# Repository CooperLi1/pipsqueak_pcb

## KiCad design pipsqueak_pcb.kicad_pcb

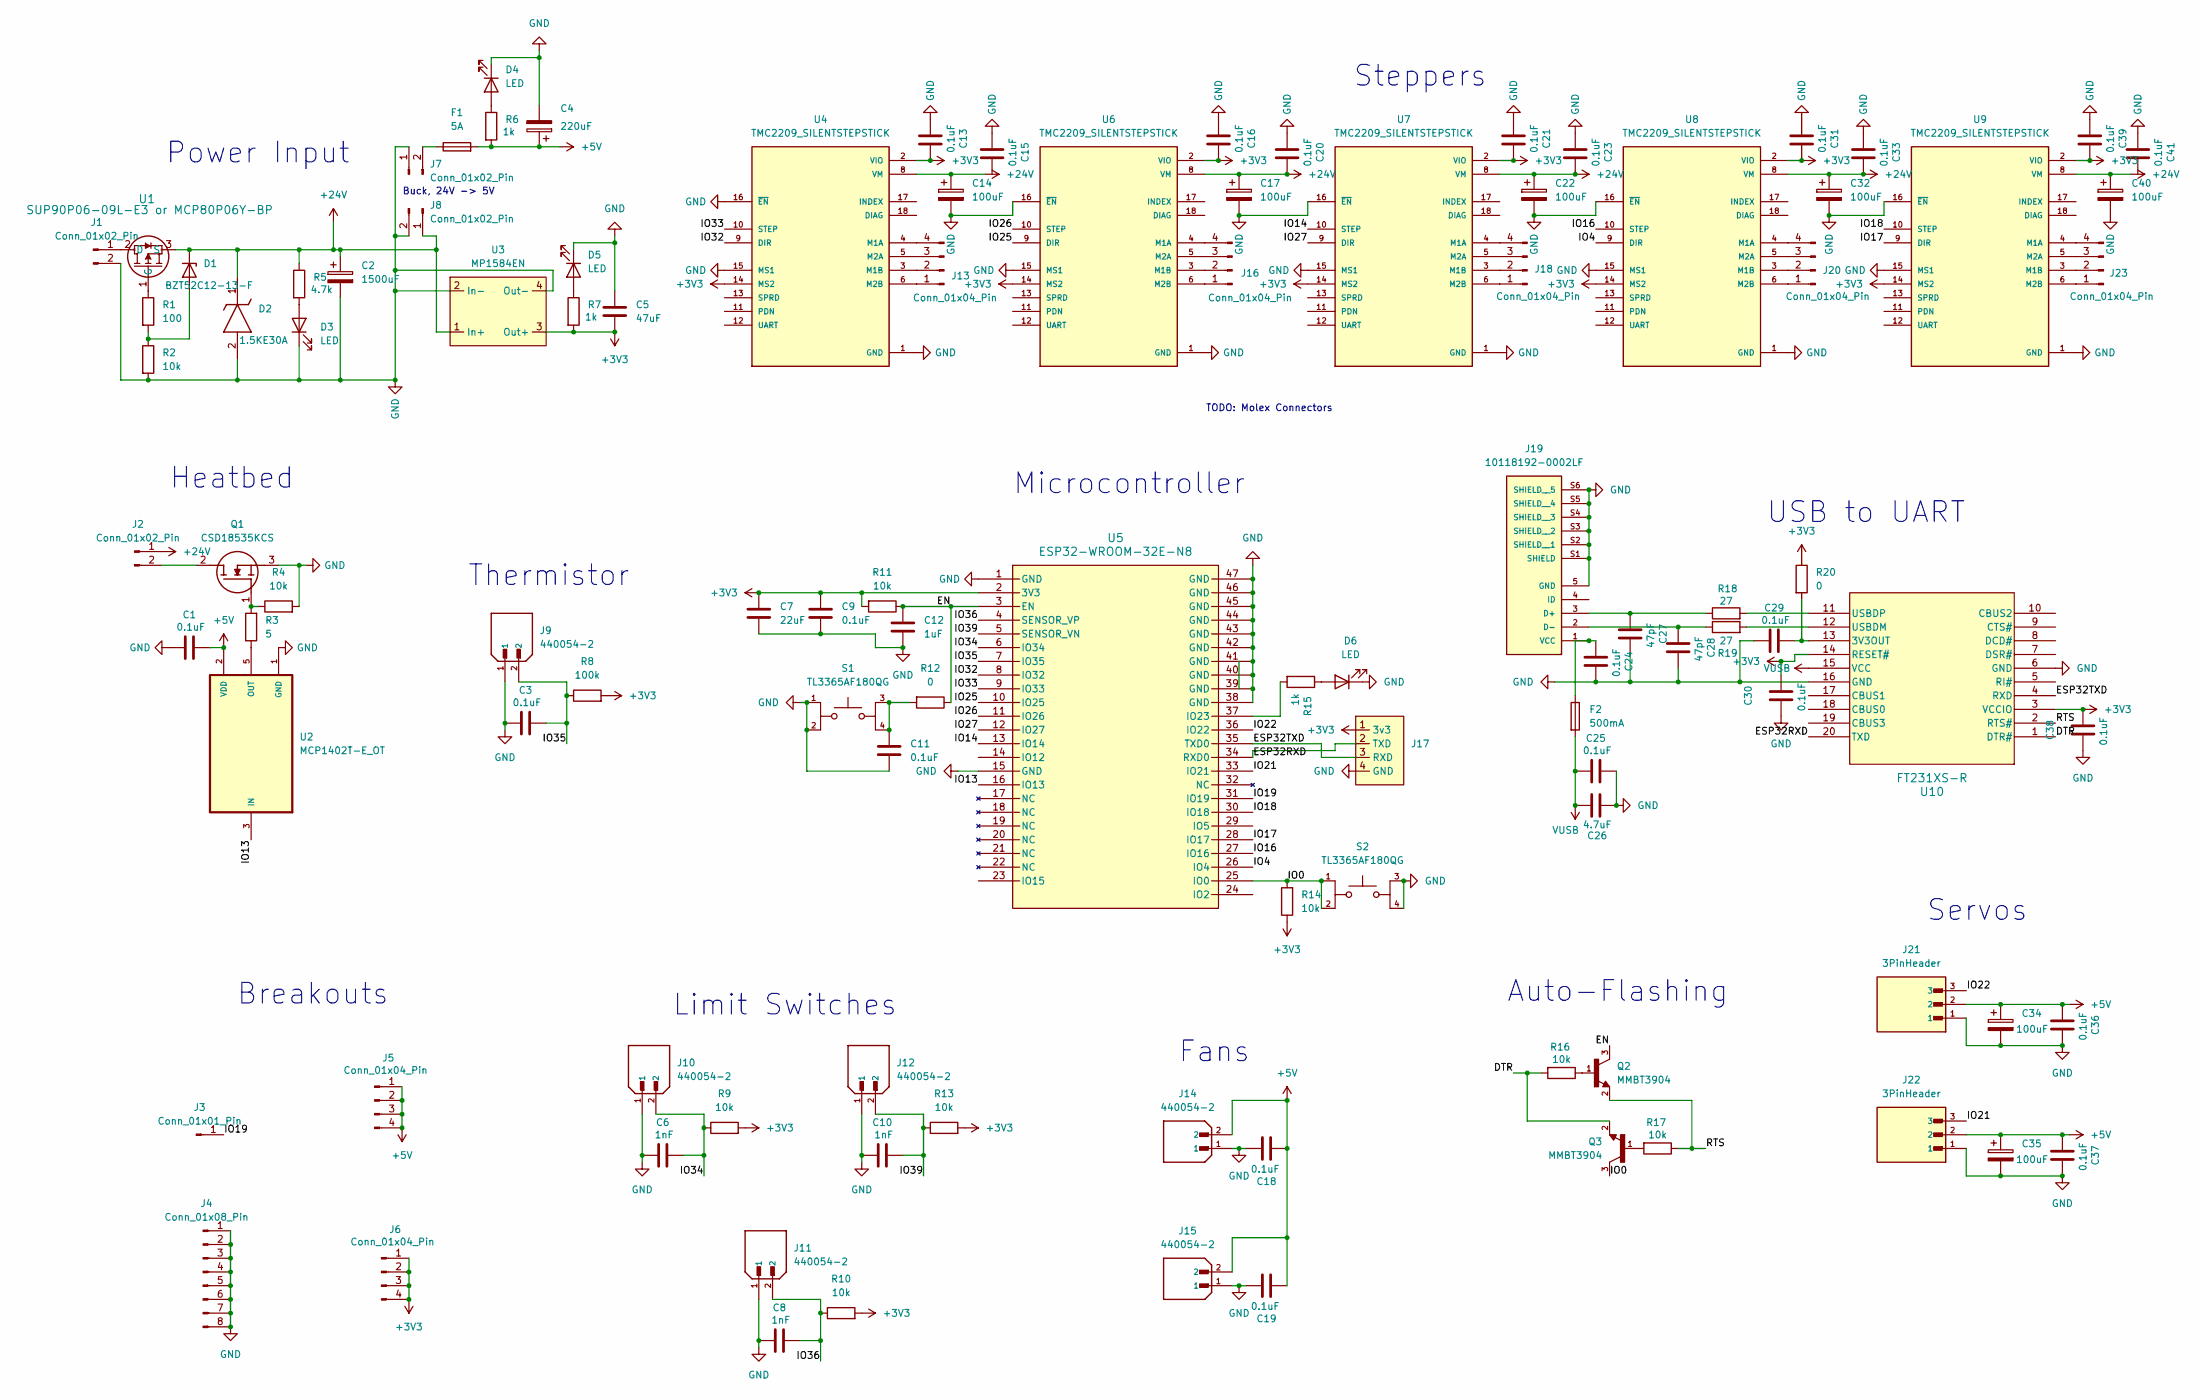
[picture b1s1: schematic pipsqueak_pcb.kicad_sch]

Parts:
C1, C3, C9, C11, C13, C15, C16, C18, C19, C20, C21, C23, C24, C25, C29, C30, C31, C33, C36, C37, C38, C39, C41: 0.1uF; C_0603_1608Metric
C2: 1500uF; CP_Radial_D18.0mm_P7.50mm
C4: 220uF; C_Elec_6.3x7.7
C5: 47uF; C_1206_3216Metric
C6, C8, C10: 1nF; C_0603_1608Metric
C7: 22uF; C_1206_3216Metric
C12: 1uF; C_0603_1608Metric
C14, C17, C22, C32, C40: 100uF; CP_Radial_D8.0mm_P3.50mm
C26: 4.7uF; C_1206_3216Metric
C27, C28: 47pF; C_0603_1608Metric
C34, C35: 100uF; CP_Elec_6.3x5.4
D1: BZT52C12-13-F; D_SOD-123
D2: 1.5KE30A; DIOAD2920W106L900D505; Mouser Part Number 511-1.5KE30A
D3, D4, D5, D6: LED; LED_0805_2012Metric
F1: 5A; Fuse_2920_7451Metric
F2: 500mA; Fuse_1812_4532Metric
J1, J2: Conn_01x02_Pin; AMASS_XT30U-F_1x02_P5.0mm_Vertical
J3: Conn_01x01_Pin; PinHeader_1x01_P2.54mm_Vertical
J4: Conn_01x08_Pin; PinHeader_1x08_P2.54mm_Vertical
J5, J6: Conn_01x04_Pin; PinHeader_1x04_P2.54mm_Vertical
J7, J8: Conn_01x02_Pin; Molex_KK-254_AE-6410-02A_1x02_P2.54mm_Vertical
J9, J10, J11, J12, J14, J15: 440054-2; TE_440054-2; PARTREV F9
J13, J16, J18, J20, J23: Conn_01x04_Pin; Molex_KK-254_AE-6410-04A_1x04_P2.54mm_Vertical
J17: 4HoleHeader
J19: 10118192-0002LF; AMPHENOL_10118192-0002LF; PARTREV B
J21, J22: 3PinHeader; HARWIN_M20-9990346
Q1: CSD18535KCS; TO254P470X1016X1611-3P; Mouser Part Number 595-CSD18535KCS
Q2, Q3: MMBT3904; TRANS_MMBT3904; PARTREV 2025-06-30
R1: 100; R_1206_3216Metric
R2, R4, R9, R10, R11, R13, R14, R16, R17: 10k; R_0603_1608Metric
R3: 5; R_0805_2012Metric
R5: 4.7k; R_0603_1608Metric
R6, R7, R15: 1k; R_0603_1608Metric
R8: 100k; R_0603_1608Metric
R12: 0; R_0603_1608Metric
R18, R19: 27; R_0603_1608Metric
R20: 0; R_1206_3216Metric_Pad1.30x1.75mm_HandSolder
S1, S2: TL3365AF180QG; SW_TL3365AF180QG; PARTREV A
U1: SUP90P06-09L-E3 or MCP80P06Y-BP; TO-220AB_VIS
U2: MCP1402T-E_OT; SOT95P270X145-5N
U3: MP1584EN
U4, U6, U7, U8, U9: TMC2209_SILENTSTEPSTICK; MODULE_TMC2209_SILENTSTEPSTICK; PARTREV 1.20
U5: ESP32-WROOM-32E-N8; ESP32­WROOM­32E_EXP
U10: FT231XS-R; SSOP-20_FTD

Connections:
+3V3: C5.2, C7.1, C9.1, C13.2, C16.2, C21.2, C30.1, C31.2, C38.1, C39.2, J6.1, J6.2, J6.3, J6.4, J17.1 (3v3), R7.2, R8.2, R9.2, R10.2, R11.2, R13.2, R14.1, R20.1, U3.3 (Out+), U4.2 (VIO), U4.14 (MS2), U5.2 (3V3), U6.2 (VIO), U6.14 (MS2), U7.2 (VIO), U7.14 (MS2), U8.2 (VIO), U8.14 (MS2), U9.2 (VIO), U9.14 (MS2), U10.3 (VCCIO), U10.14 (RESET#)
+5V: C1.1, C4.1, C18.2, C19.2, C34.1, C35.1, C36.2, C37.2, F1.2, J5.1, J5.2, J5.3, J5.4, J14.2, J15.2, J21.2, J22.2, R6.2, U2.2 (VDD)
+24V: C2.1, C14.1, C17.1, C20.2, C22.1, C23.2, C32.1, C33.2, C40.1, D1.1 (K), D2.1 (K), J2.1, J8.1, R5.1, U1.3 (S), U3.1 (In+), U4.8 (VM), U6.8 (VM), U7.8 (VM), U8.8 (VM), U9.8 (VM)
/DTR: Q3.2, R16.2, U10.1 (DTR#)
/EN: C12.1, Q2.3, R11.1, R12.1, U5.3 (EN)
/ESP32RXD: J17.2 (TXD), U5.34 (RXD0), U10.20 (TXD)
/ESP32TXD: J17.3 (RXD), U5.35 (TXD0), U10.4 (RXD)
/IO0: Q3.3, R14.2, S2.1, S2.2, U5.25 (IO0)
/IO4: U5.26 (IO4), U8.9 (DIR)
/IO13: U2.3 (IN), U5.16 (IO13)
/IO14: U5.13 (IO14), U7.10 (STEP)
/IO16: U5.27 (IO16), U8.10 (STEP)
/IO17: U5.28 (IO17), U9.9 (DIR)
/IO18: U5.30 (IO18), U9.10 (STEP)
/IO19: J3.1, U5.31 (IO19)
/IO21: J22.3, U5.33 (IO21)
/IO22: J21.3, U5.36 (IO22)
/IO25: U5.10 (IO25), U6.9 (DIR)
/IO26: U5.11 (IO26), U6.10 (STEP)
/IO27: U5.12 (IO27), U7.9 (DIR)
/IO32: U4.9 (DIR), U5.8 (IO32)
/IO33: U4.10 (STEP), U5.9 (IO33)
/IO34: C6.1, J10.2, R9.1, U5.6 (IO34)
/IO35: C3.1, J9.2, R8.1, U5.7 (IO35)
/IO36: C8.1, J11.2, R10.1, U5.4 (SENSOR_VP)
/IO39: C10.1, J12.2, R13.1, U5.5 (SENSOR_VN)
/RTS: Q2.2, R17.1, U10.2 (RTS#)
GND: C1.2, C2.2, C3.2, C4.2, C5.1, C6.2, C7.2, C8.2, C9.2, C10.2, C11.1, C12.2, C13.1, C14.2, C15.1, C16.1, C17.2, C18.1, C19.1, C20.1, C21.1, C22.2, C23.1, C24.1, C25.1, C26.1, C27.1, C28.1, C29.2, C30.2, C31.1, C32.2, C33.1, C34.2, C35.2, C36.1, C37.1, C38.2, C39.1, C40.2, C41.1, D2.2 (A), D3.1 (K), D4.1 (K), D5.1 (K), D6.1 (K), J1.2, J4.1, J4.2, J4.3, J4.4, J4.5, J4.6, J4.7, J4.8, J7.1, J8.2, J9.1, J10.1, J11.1, J12.1, J14.1, J15.1, J17.4 (GND), J19.5 (GND), J19.S1 (SHIELD), J19.S2 (SHIELD__1), J19.S3 (SHIELD__2), J19.S4 (SHIELD__3), J19.S5 (SHIELD__4), J19.S6 (SHIELD__5), J21.1, J22.1, Q1.3 (S), R2.2, R4.2, S1.1, S1.2, S2.3, S2.4, U2.1 (GND), U2.4 (GND), U3.2 (In-), U3.4 (Out-), U4.1 (GND), U4.7 (GND), U4.15 (MS1), U4.16 (~EN), U5.1 (GND), U5.15 (GND), U5.38 (GND), U5.39 (GND), U5.40 (GND), U5.41 (GND), U5.42 (GND), U5.43 (GND), U5.44 (GND), U5.45 (GND), U5.46 (GND), U5.47 (GND), U6.1 (GND), U6.7 (GND), U6.15 (MS1), U6.16 (~EN), U7.1 (GND), U7.7 (GND), U7.15 (MS1), U7.16 (~EN), U8.1 (GND), U8.7 (GND), U8.15 (MS1), U8.16 (~EN), U9.1 (GND), U9.7 (GND), U9.15 (MS1), U9.16 (~EN), U10.6 (GND), U10.16 (GND)
unnamed: C11.2, R12.2, S1.3, S1.4
unnamed: D1.2 (A), R1.2, R2.1
unnamed: D3.2 (A), R5.2
unnamed: D4.2 (A), R6.1
unnamed: D5.2 (A), R7.1
unnamed: D6.2 (A), R15.1
unnamed: J1.1, U1.2 (D)
unnamed: J2.2, Q1.2 (D)
unnamed: F1.1, J7.2
unnamed: J13.1, U4.6 (M2B)
unnamed: J13.2, U4.3 (M1B)
unnamed: J13.3, U4.5 (M2A)
unnamed: J13.4, U4.4 (M1A)
unnamed: J16.1, U6.6 (M2B)
unnamed: J16.2, U6.3 (M1B)
unnamed: J16.3, U6.5 (M2A)
unnamed: J16.4, U6.4 (M1A)
unnamed: J18.1, U7.6 (M2B)
unnamed: J18.2, U7.3 (M1B)
unnamed: J18.3, U7.5 (M2A)
unnamed: J18.4, U7.4 (M1A)
unnamed: C27.2, J19.3 (D+), R18.1
unnamed: C28.2, J19.2 (D-), R19.1
unnamed: C24.2, F2.1, J19.1 (VCC)
unnamed: J20.1, U8.6 (M2B)
unnamed: J20.2, U8.3 (M1B)
unnamed: J20.3, U8.5 (M2A)
unnamed: J20.4, U8.4 (M1A)
unnamed: J23.1, U9.6 (M2B)
unnamed: J23.2, U9.3 (M1B)
unnamed: J23.3, U9.5 (M2A)
unnamed: J23.4, U9.4 (M1A)
unnamed: Q1.1 (G), R3.2, R4.1
unnamed: Q2.1, R16.1
unnamed: Q3.1, R17.2
unnamed: R1.1, U1.1 (G)
unnamed: R3.1, U2.5 (OUT)
unnamed: R15.2, U5.37 (IO23)
unnamed: C29.1, R20.2, U10.13 (3V3OUT)
unnamed: R19.2, U10.12 (USBDM)
unnamed: R18.2, U10.11 (USBDP)
VUSB: C25.2, C26.2, F2.2, U10.15 (VCC)

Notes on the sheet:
Heatbed
Buck, 24V -> 5V
USB to UART
Limit Switches
Breakouts
TODO: Molex Connectors
Fans
Steppers
Power Input
Thermistor
Microcontroller
Servos
Auto-Flashing

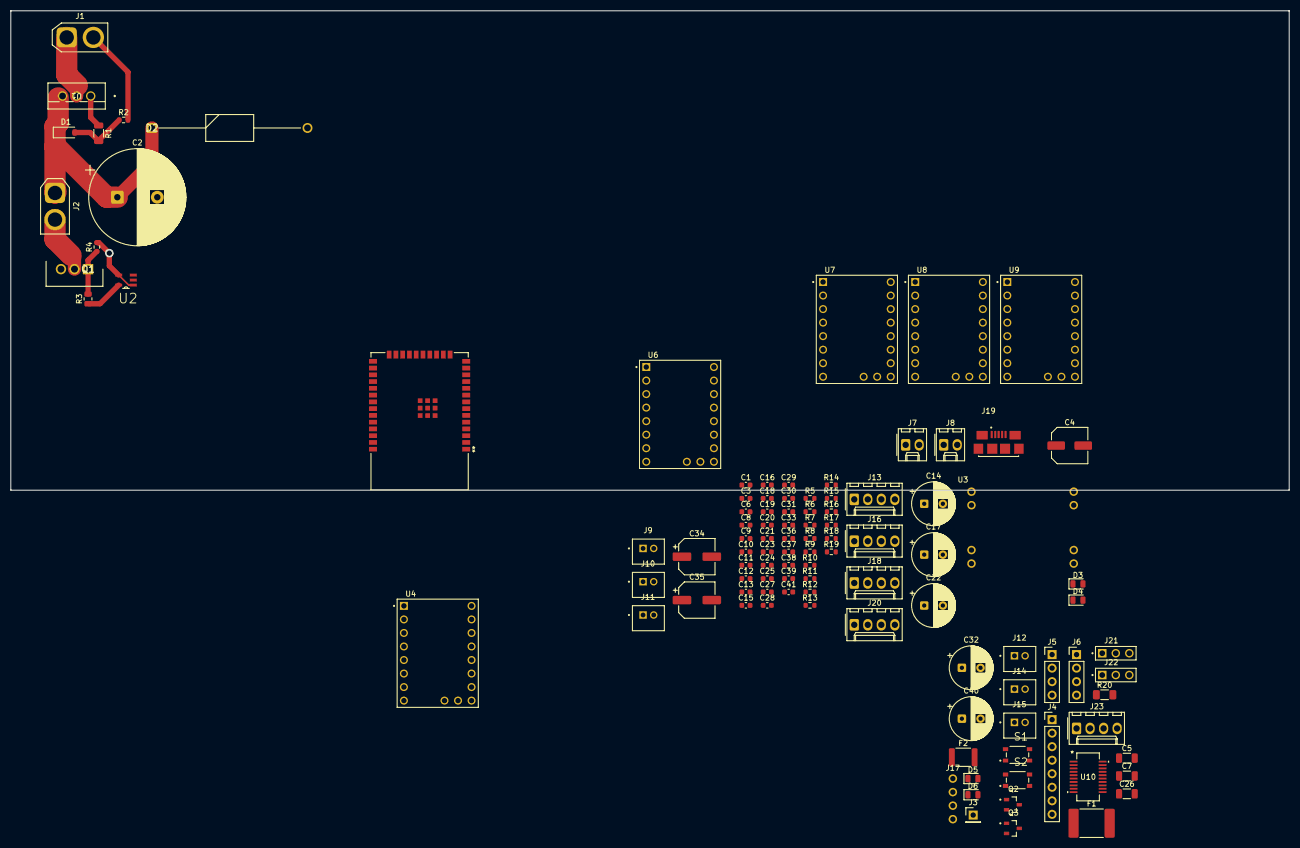
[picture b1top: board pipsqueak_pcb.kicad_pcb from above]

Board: 2 copper layers, 240.0 x 90.0 mm, 107 parts (0 on the bottom side), 70 nets.

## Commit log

2026-05-12 schematic finished
2026-05-12 pca fix
2026-05-14 finished
